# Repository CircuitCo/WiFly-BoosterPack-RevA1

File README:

The WiFly BoosterPack equips your Launchpad with the ability to connect to 802.11b/g wireless networks.  The design uses the Launchpad's UART hardware to interface to Roving Network's RN171XV ultra-low power embedded TCP/IP module.  An external antenna can be attached via a standard RP-SMA connector. Due to its small form factor and extremely low power consumption, it is perfect for mobile wireless applications such as asset monitoring, sensors, and portable battery operated devices. The WiFly BoosterPack is compatible with the MSP430 LaunchPad and Tiva C LaunchPad (previously Stellaris). This board is designed by Sakoman Inc. For more information on the designer please visit http://www.sakoman.com/.

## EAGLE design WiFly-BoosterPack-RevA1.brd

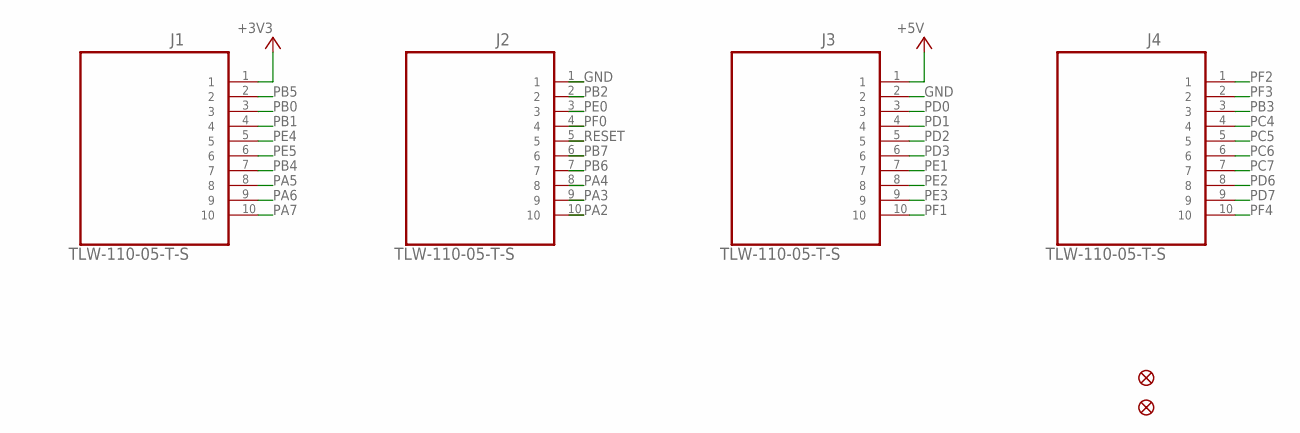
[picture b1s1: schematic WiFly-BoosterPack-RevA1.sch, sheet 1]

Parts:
FID1, FID2: FIDUCIAL1X2; FIDUCIAL-1X2
J1: TLW-110-05-T-S; SAMTEC_TLW-110-05-T-S
J2, J3, J4: TLW-110-05-T-S; SAMTEC_TLW-110-05-T-S; MPN TLW-110-05-T-S

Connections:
+3V3: J1.1; also elsewhere on the board
+5V: J3.1
GND: J2.1, J3.2; also elsewhere on the board
PA2: J2.10
PA3: J2.9
PA4: J2.8
PA5: J1.8
PA6: J1.9
PA7: J1.10
PB0: J1.3; also elsewhere on the board
PB1: J1.4; also elsewhere on the board
PB2: J2.2
PB3: J4.3
PB4: J1.7
PB5: J1.2
PB6: J2.7
PB7: J2.6
PC4: J4.4; also elsewhere on the board
PC5: J4.5; also elsewhere on the board
PC6: J4.6
PC7: J4.7
PD0: J3.3
PD1: J3.4
PD2: J3.5
PD3: J3.6
PD6: J4.8
PD7: J4.9
PE0: J2.3
PE1: J3.7
PE2: J3.8
PE3: J3.9
PE4: J1.5
PE5: J1.6
PF0: J2.4
PF1: J3.10
PF2: J4.1
PF3: J4.2
PF4: J4.10
RESET: J2.5

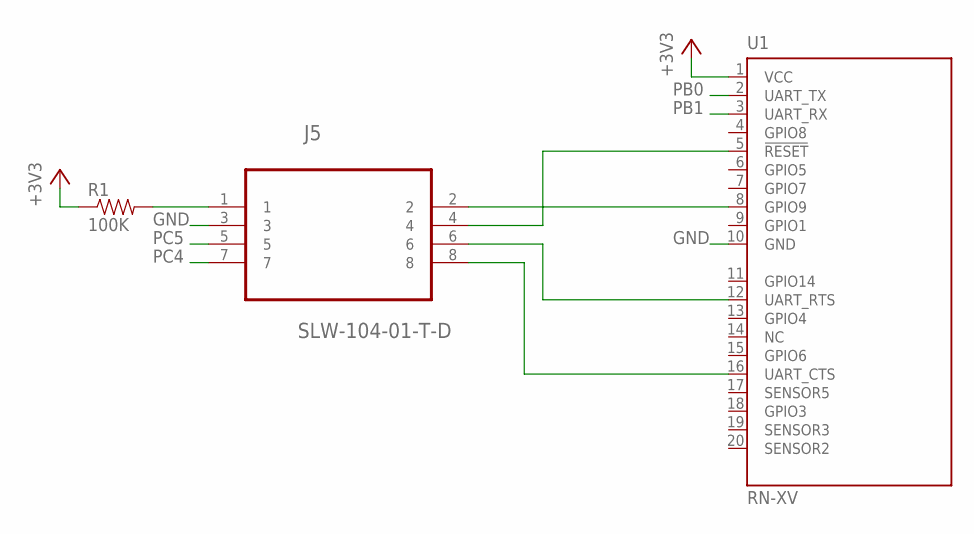
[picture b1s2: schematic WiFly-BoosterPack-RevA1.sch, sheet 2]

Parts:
J5: SLW-104-01-T-D; SAMTEC_SLW-104-01-T-D
R1: 100K; AXIAL-0.3
U1: RN-XV; RN-VX

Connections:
+3V3: R1.P$1 (1), U1.1 (VCC); also elsewhere on the board
GND: J5.3, U1.10 (GND); also elsewhere on the board
unnamed: J5.1, R1.P$2 (2)
unnamed: J5.2, U1.8 (GPIO9)
unnamed: J5.4, U1.5 (!RESET)
unnamed: J5.6, U1.12 (UART_RTS)
unnamed: J5.8, U1.16 (UART_CTS)
PB0: U1.2 (UART_TX); also elsewhere on the board
PB1: U1.3 (UART_RX); also elsewhere on the board
PC4: J5.7; also elsewhere on the board
PC5: J5.5; also elsewhere on the board

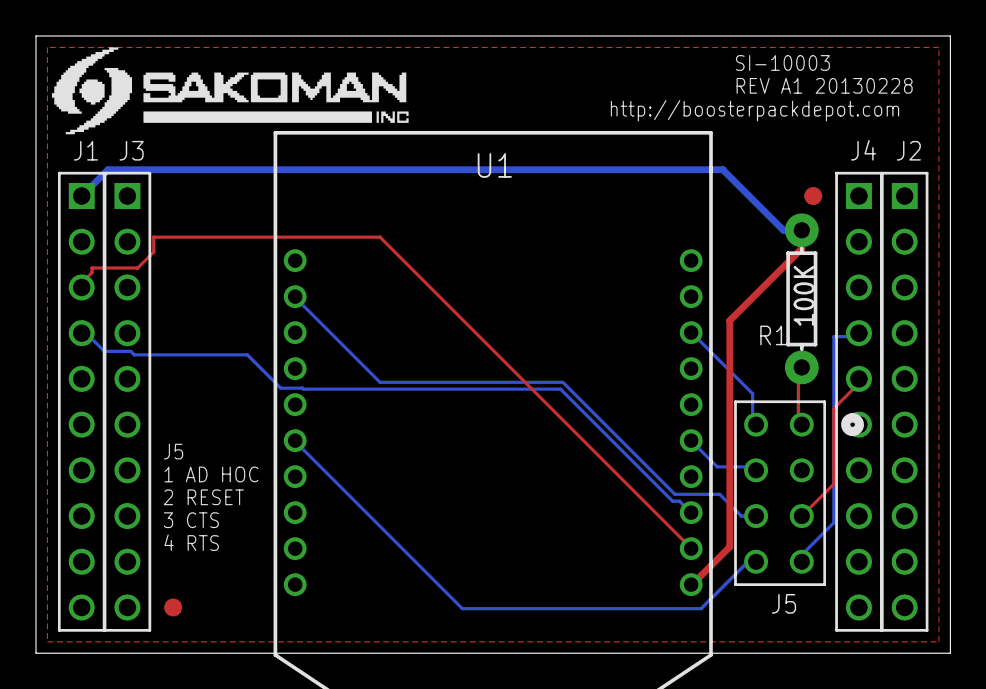
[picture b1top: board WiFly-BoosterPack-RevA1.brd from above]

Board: 2 copper layers, 50.8 x 34.3 mm, 9 parts (0 on the bottom side), 11 nets.

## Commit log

2013-09-11 init-commit

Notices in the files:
parts and their libraries:
SparkFun-Resistors: Licensing: CC v3.0 Share-Alike You are welcome to use this library for commercial purposes.
